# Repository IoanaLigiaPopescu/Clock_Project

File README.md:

BOM

Reference | Qty | Value / Part | JLC Parts Link | Datasheet
U1 | 1 | nRF52840 | https://jlcpcb.com/parts/componentSearch?searchTxt=nRF52840 | https://infocenter.nordicsemi.com/pdf/nRF52840_PS_v1.1.pdf
IC1 | 1 | BQ25180YBGR | https://jlcpcb.com/parts/componentSearch?searchTxt=BQ25180YBGR | https://www.ti.com/lit/ds/symlink/bq25180.pdf
IC2 | 1 | DRV2605YZFR | https://jlcpcb.com/parts/componentSearch?searchTxt=DRV2605YZFR | https://www.ti.com/lit/ds/symlink/drv2605.pdf
IC3 | 1 | BMA421 | https://jlcpcb.com/parts/componentSearch?searchTxt=BMA421 | https://www.bosch-sensortec.com/media/boschsensortec/downloads/datasheets/bst-bma421-ds000.pdf
IC9 | 1 | RT6160AWSC | https://jlcpcb.com/parts/componentSearch?searchTxt=RT6160AWSC | https://www.richtek.com/assets/product_file/RT6160A/DS6160A-00.pdf
U3 | 1 | MAX17048G+T10 | https://jlcpcb.com/parts/componentSearch?searchTxt=MAX17048G+T10 | https://www.analog.com/media/en/technical-documentation/data-sheets/MAX17048-MAX17049.pdf
D3 | 1 | USBLC6-2SC6Y | https://jlcpcb.com/parts/componentSearch?searchTxt=USBLC6-2SC6Y | https://www.st.com/resource/en/datasheet/usblc6-2.pdf
Q1 | 1 | DMG2305UX-7 | https://jlcpcb.com/parts/componentSearch?searchTxt=DMG2305UX-7 | https://www.diodes.com/assets/Datasheets/DMG2305UX.pdf
Q3 | 1 | SI1308EDL-T1-GE3 | https://jlcpcb.com/parts/componentSearch?searchTxt=SI1308EDL | https://www.vishay.com/docs/63399/si1308edl.pdf
J1 | 1 | 503480-2400 | https://jlcpcb.com/parts/componentSearch?searchTxt=503480-2400 | https://www.molex.com/pdm_docs/sd/5034802400_sd.pdf
J2 | 1 | TC2030-IDC | https://jlcpcb.com/parts/componentSearch?searchTxt=TC2030-IDC | https://www.tag-connect.com/wp-content/uploads/bsk-pdf-manager/TC2030-IDC-NL.pdf
J4 | 1 | KH-TYPE-C-16P | https://jlcpcb.com/parts/componentSearch?searchTxt=KH-TYPE-C-16P | https://www.kinghelm.net/uploadfiles/file/20231201/KH-TYPE-C-16P.pdf
ANT1 | 1 | 2450AT18B100E | https://jlcpcb.com/parts/componentSearch?searchTxt=2450AT18B100E | https://www.kyocera-avx.com/docs/techinfo/2450AT18B100.pdf
L7 | 1 | FTC252012SR47MBCA | https://jlcpcb.com/parts/componentSearch?searchTxt=FTC252012SR47MBCA | https://www.fenghua-advanced.com/upload/FTC252012.pdf
SW_DN,SW_ENT,SW_UP | 3 | EVP-AKE31A | https://jlcpcb.com/parts/componentSearch?searchTxt=EVP-AKE31A | https://industrial.panasonic.com/cdbs/www-data/pdf/ABH0000/ABH0000CE116.pdf
X1 | 1 | 32MHz Crystal | https://jlcpcb.com/parts/componentSearch?searchTxt=32MHz crystal 2016 | https://ecsxtal.com/store/pdf/ECS-2016MV.pdf
X2 | 1 | 32.768kHz Crystal | https://jlcpcb.com/parts/componentSearch?searchTxt=32.768kHz crystal 3215 | https://abracon.com/Resonators/ABS07.pdf
C* | multiple | Capacitors 0201/0402 | https://jlcpcb.com/parts/componentSearch?searchTxt=capacitor 0402 | https://www.murata.com/products/productdata/8796745949214/mlcc02e.pdf
R* | multiple | Resistors 0201 | https://jlcpcb.com/parts/componentSearch?searchTxt=resistor 0201 | https://www.yageo.com/upload/media/product/productsearch/datasheet/rchip/PYu-RC_Group_51_RoHS_L_12.pdf
L1,L2,L3,L5 | multiple | Inductors SMD | https://jlcpcb.com/parts/componentSearch?searchTxt=smd inductor | https://www.murata.com/products/productdata/8797098139678/ENFA0008.pdf
TP* | 14 | Test Pads | https://jlcpcb.com/parts/componentSearch?searchTxt=test pad pcb | https://www.keystone-europe.com/downloads/datasheets/5000.pdf

FUNCTIONALITATE

Proiectul este o platformă embedded portabilă bazată pe microcontroller-ul nRF52840, proiectată pentru aplicații low-power cu interfață vizuală E-Paper, alimentare din baterie Li-Po, conectivitate USB-C, feedback haptic și senzori de mișcare. Toate componentele sunt montate pe stratul Top al plăcii PCB.

Microcontroller-ul principal este nRF52840. Acesta integrează procesor ARM Cortex-M4F la 64 MHz, memorie Flash 1 MB, RAM 256 KB și transceiver radio 2.4 GHz compatibil Bluetooth Low Energy. Comunicarea RF se realizează printr-o antenă ceramică 2.45 GHz conectată printr-o rețea de adaptare de impedanță formată din L1, C3, C4 și pad opțional C22 pentru tuning RF. Oscilatorul principal extern este de 32 MHz (X1), iar oscilatorul low-power RTC este de 32.768 kHz (X2).

Interfața USB este realizată prin conector USB Type-C J4. Liniile D+ și D- sunt conectate direct la microcontroller pentru comunicație USB Full Speed. Pinii CC1 și CC2 sunt configurați prin rezistențe de 5.1 kΩ la masă pentru mod Device. Protecția ESD a liniilor USB este realizată de componenta USBLC6-2SC6Y.

Alimentarea principală provine din baterie Li-Po reîncărcabilă. Circuitul de încărcare este BQ25180YBGR, care gestionează încărcarea de la VBUS (5 V USB), controlul curentului de încărcare și monitorizarea stării prin interfață I2C. Tensiunea bateriei este disponibilă pe net-ul BAT și filtrată local prin condensatorul C39.

Conversia de tensiune este realizată de RT6160AWSC, convertor buck-boost controlat prin I2C. Acesta poate ridica sau coborî tensiunea bateriei pentru a genera rail-ul stabilizat necesar sistemului. Etajul de putere utilizează inductanța L7 și condensatorii C23, C24 la intrare respectiv C25, C32 la ieșire.

Monitorizarea nivelului bateriei este realizată de MAX17048G+T10, fuel gauge conectat la magistrala I2C. Acesta măsoară tensiunea celulei și estimează procentul de încărcare, oferind semnal ALERT către microcontroller.

Senzorul de mișcare utilizat este BMA421, accelerometru triaxial low-power. Comunicarea cu microcontroller-ul se face prin I2C, iar liniile INT1 și INT2 permit detectarea de evenimente precum mișcare, tap sau wake-up. Alimentarea senzorului este filtrată prin C18 și C19.

Feedback-ul tactil este realizat prin DRV2605YZFR, driver dedicat pentru motoare ERM/LRA. Acesta este controlat prin I2C și poate genera modele de vibrație prestabilite. Ieșirile OUT+ și OUT- sunt rutate către test point-urile TP_OP și TP_ON.

Interfața vizuală este un display E-Paper conectat prin conector FPC J1 cu 24 pini. Controlul se face de la microcontroller prin semnale dedicate (SPI și GPIO), inclusiv EPD_CS. Circuitul auxiliar al display-ului folosește MOSFET-ul Q3 și componente pasive dedicate pentru generarea tensiunilor necesare panoului.

Interfața utilizator este compusă din trei butoane tactile SW_UP, SW_ENT și SW_DN, conectate la GPIO-urile microcontroller-ului. Acestea permit navigare în meniu și control local fără dispozitive externe.

Programarea și depanarea hardware se realizează prin conectorul J2 compatibil SWD. Sunt disponibile liniile SWDIO, SWDCLK, RESET și SWO. În plus, placa include multiple test point-uri pentru 3.3V, GND, VBAT, SDA, SCL și alte semnale utile în validare.

Magistrala principală de comunicație internă este I2C, partajată între charger, convertorul DC/DC, fuel gauge, IMU și driverul haptic. Aceasta reduce numărul de pini utilizați și simplifică layout-ul PCB.

Estimarea consumului de energie depinde de modul de operare. nRF52840 în sleep poate coborî la ordinul microamperilor. În transmisie radio consumul este de ordinul miliamperilor. Display-ul E-Paper consumă aproape zero în regim static și energie doar la refresh. IMU-ul BMA421 funcționează în mod low-power la câțiva microamperi. Driverul haptic consumă semnificativ doar în timpul vibrației. Autonomia sistemului este favorizată de utilizarea componentelor low-power și a afișajului bistabil.

PCB-ul este proiectat pe 4 straturi, cu planuri dedicate de masă pentru integritate de semnal, zgomot redus și performanță RF mai bună. Toate componentele sunt plasate pe stratul superior pentru asamblare simplificată SMT.

PINI

nRF52840 este microcontroller-ul principal al sistemului și controlează toate perifericele hardware: alimentare, senzori, display, comunicație USB și debugging. Alegerea pinilor a fost făcută pentru a folosi interfețele hardware dedicate și pentru a simplifica rutarea PCB.

Pinii D+ și D- sunt conectați la conectorul USB-C prin protecția ESD D3. Aceștia sunt utilizați pentru comunicație USB nativă, programare și transfer de date.

Pinii SWDIO, SWDCLK, RESET și SWO sunt scoși la conectorul J2 pentru programare și debugging hardware.

P0.07 și P0.08 sunt utilizați ca SDA și SCL pentru magistrala I2C. Pe această magistrală sunt conectate BQ25180 (charger), RT6160A (buck-boost), MAX17048 (fuel gauge), BMA421 (IMU) și DRV2605 (driver haptic). Alegerea I2C reduce numărul de pini utilizați.

P1.08 și P1.09 sunt conectați la INT1 și INT2 de la accelerometru, pentru wake-up la mișcare și notificări hardware.

P0.11 este utilizat pentru semnal de interrupt din zona de power management.

P0.12 este utilizat pentru controlul subsistemului haptic.

P0.06 este utilizat pentru EPD_CS, semnal de selecție al display-ului E-Paper. Restul pinilor display-ului folosesc SPI și GPIO pentru control.

P0.04 și P0.05 sunt pini analogici utilizați pentru măsurători ADC, de exemplu monitorizare tensiune.

Pinul ANT este conectat la rețeaua RF L1, C3, C4 și antena ceramică. Traseul este menținut scurt pentru performanță radio bună.

XC1 și XC2 sunt conectați la cristalul de 32 MHz, iar XL1 și XL2 la cristalul de 32.768 kHz pentru RTC low-power.

PCB-ul este pe 4 straturi, cu plane de masă dedicate și toate componentele pe Top Layer. Antena este plasată la marginea plăcii cu keepout RF. Zona de alimentare este separată de zona RF, iar test point-urile pentru 3.3V, GND, VBAT, SWD și I2C permit depanare rapidă. Designul este optimizat pentru consum redus și funcționare pe baterie.

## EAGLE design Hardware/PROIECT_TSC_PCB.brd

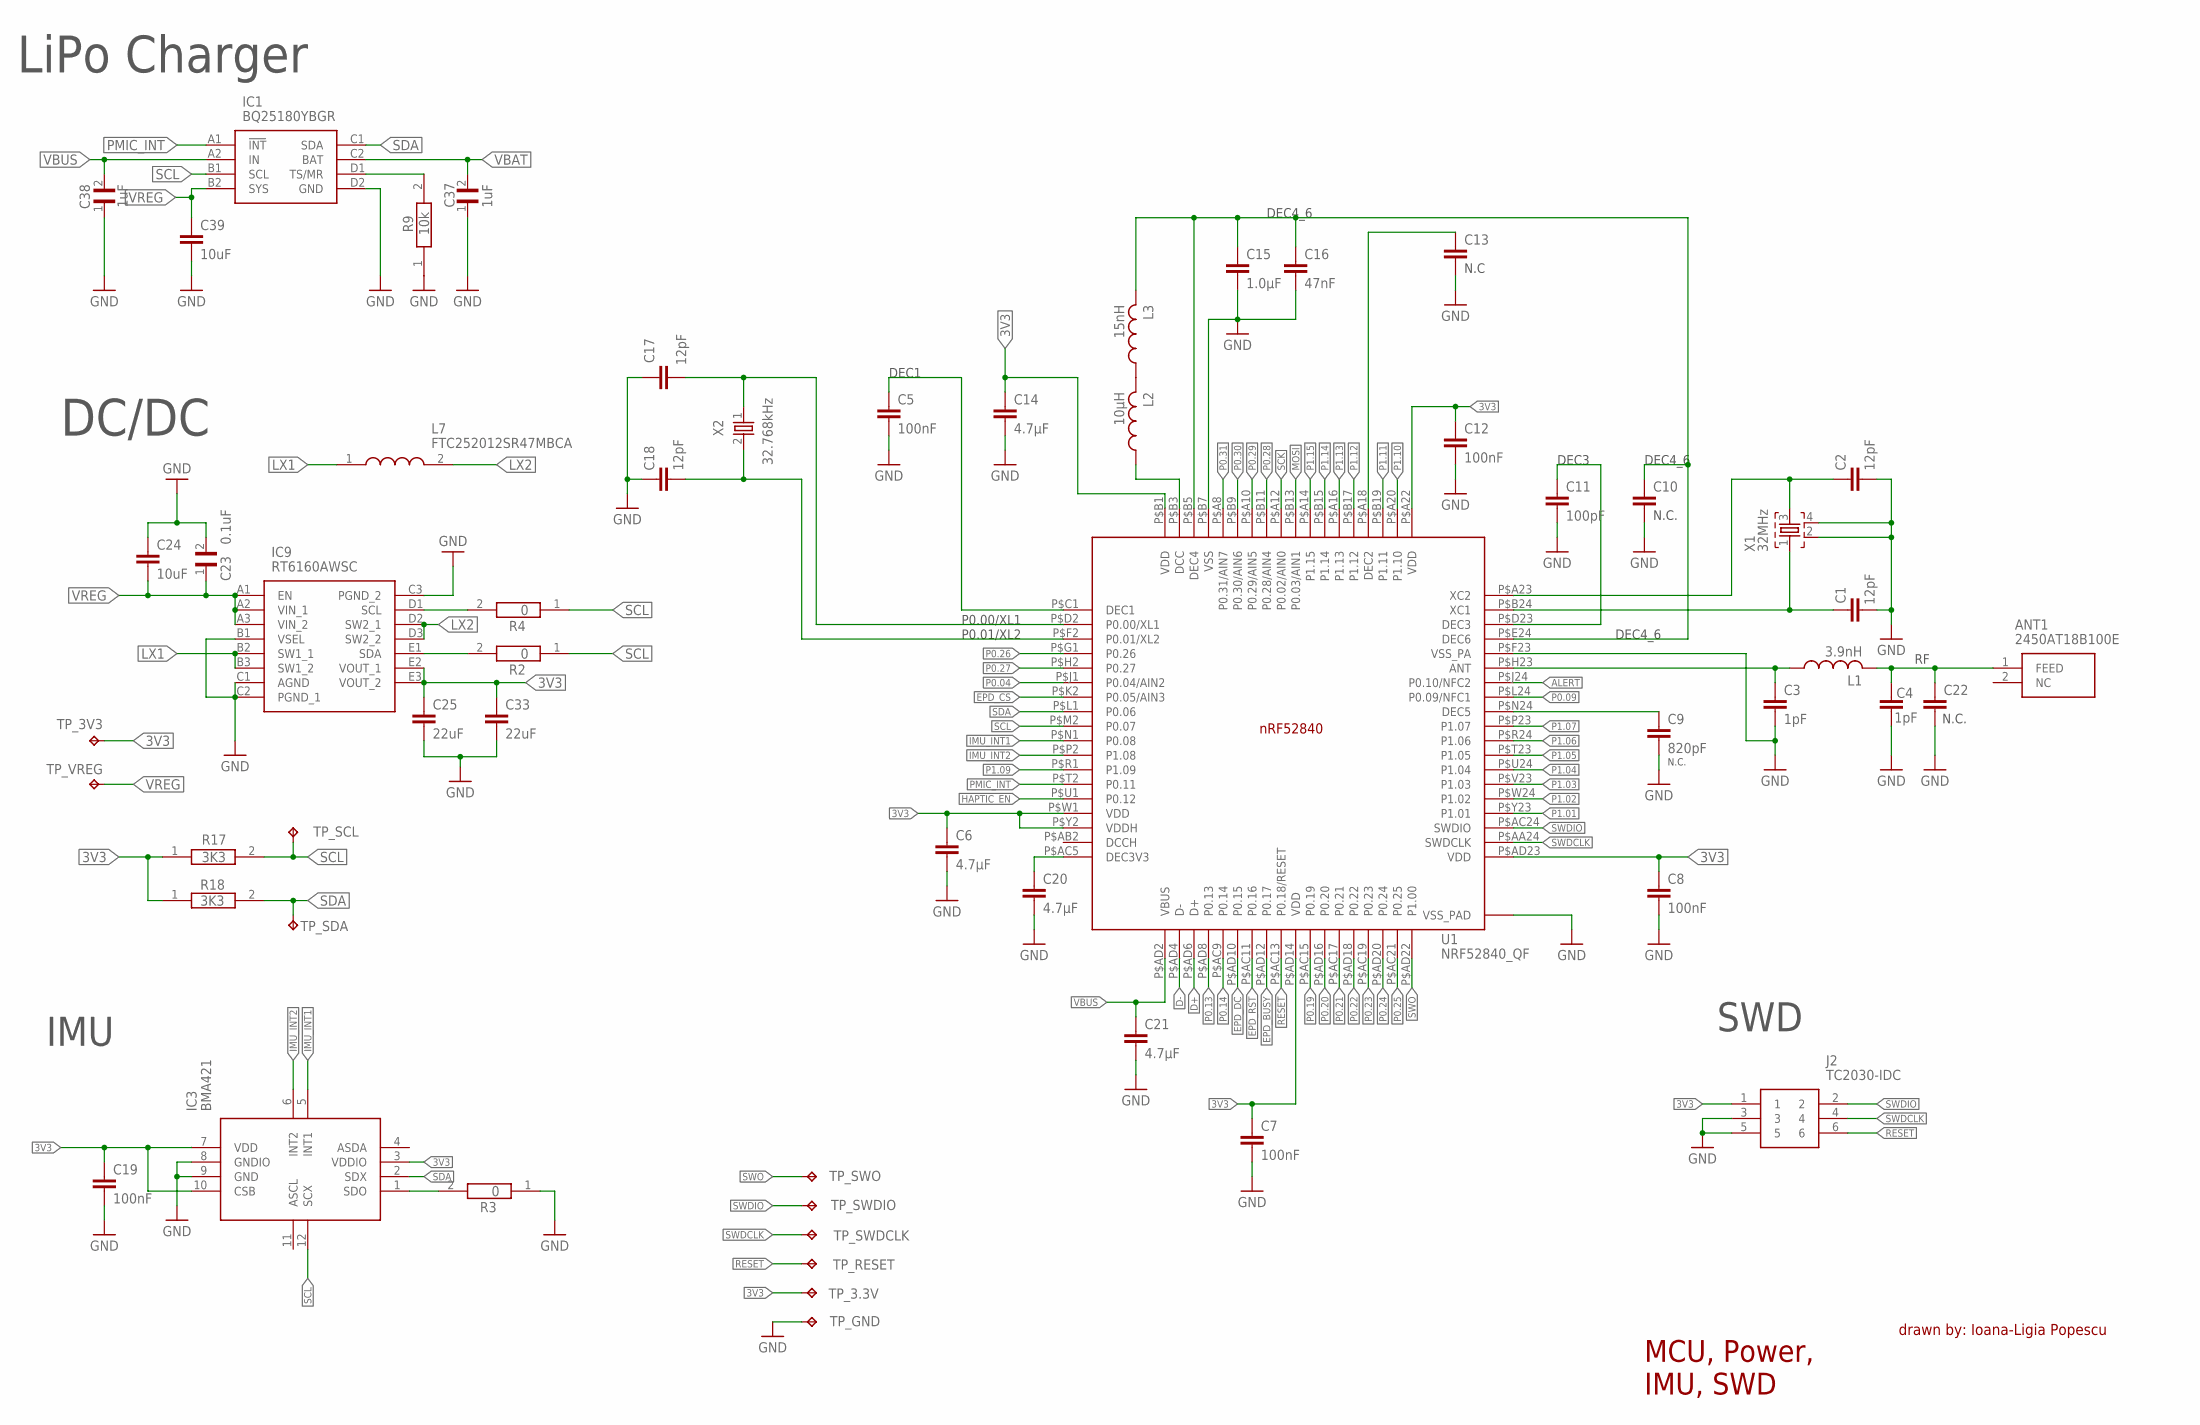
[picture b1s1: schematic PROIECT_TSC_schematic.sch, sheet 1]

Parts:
ANT1: 2450AT18B100E; 2450AT18B100E_ANTC3216X140N
C1, C2, C17, C18: 12pF; NORDIC_NRF_3_RESC0201_L
C3, C4: 1pF; NORDIC_NRF_3_RESC0201_L
C5, C7, C8, C12, C19: 100nF; NORDIC_NRF_3_RESC0201_L
C6, C14, C20, C21: 4.7µF; ESP32_C6_LIBRARY_1_ESP32_WROVER_EAGLE-LTSPICE_C0402
C9: 820pF; NORDIC_NRF_3_RESC0201_L
C10, C13, C22: NORDIC_NRF_3_CAPACITOR_0201_L; NORDIC_NRF_3_RESC0201_L
C11: 100pF; NORDIC_NRF_3_RESC0201_L
C15: 1.0µF; ESP32_C6_LIBRARY_1_ESP32_WROVER_EAGLE-LTSPICE_C0402
C16: 47nF; NORDIC_NRF_3_RESC0201_L
C23: 0.1uF; GRM011R60J152KE01L_2_CAPC0201X13N
C24, C39: 10uF; ESP32_C6_LIBRARY_1_ESP32_WROVER_EAGLE-LTSPICE_C0402
C25, C33: 22uF; ESP32_C6_LIBRARY_1_ESP32_WROVER_EAGLE-LTSPICE_C0402
C37, C38: 1uF; GRM011R60J152KE01L_2_CAPC0201X13N
IC1: BQ25180YBGR; BQ25180YBGR_BGA8C40P2X4_100X155X50
IC3: BMA421; BMA423_BMA423
IC9: RT6160AWSC; RT6160AWSC_BGA15C40P3X5_140X230X60
J2: TC2030-IDC; TC2030-IDC_TC2030IDC
L1: 3.9nH; NORDIC_NRF_2_RESC0402_L
L2: 10µH; NORDIC_NRF_2_RESC0402_L
L3: 15nH; NORDIC_NRF_2_RESC0402_L
L7: FTC252012SR47MBCA; MLP2016SR47MT0S1_INDC2016X100N
R2, R3, R4: 0; CPF0201D7K68C1_0201
R9: 10k; CPF0201D7K68C1_0201
R17, R18: 3K3; CPF0201D7K68C1_0201
TP_3.3V, TP_3V3: HECTOR_WATCH_1_TPTP20R; HECTOR_WATCH_1_TP20R
TP_GND: HECTOR_WATCH_1_TPTP20R; HECTOR_WATCH_1_TP20R
TP_RESET: HECTOR_WATCH_1_TPTP20R; HECTOR_WATCH_1_TP20R
TP_SCL: HECTOR_WATCH_1_TPTP20R; HECTOR_WATCH_1_TP20R
TP_SDA: HECTOR_WATCH_1_TPTP20R; HECTOR_WATCH_1_TP20R
TP_SWDCLK: HECTOR_WATCH_1_TPTP20R; HECTOR_WATCH_1_TP20R
TP_SWDIO: HECTOR_WATCH_1_TPTP20R; HECTOR_WATCH_1_TP20R
TP_SWO: HECTOR_WATCH_1_TPTP20R; HECTOR_WATCH_1_TP20R
TP_VREG: HECTOR_WATCH_1_TPTP20R; HECTOR_WATCH_1_TP20R
U1: NRF52840_QF; NORDIC_NRF_4_AQFN50P700X700X85_HS-74N
X1: 32MHz; NORDIC_NRF_BT-XTAL_2016_N
X2: 32.768kHz; NORDIC_NRF_1_XTAL_3215_N

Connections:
3V3: C6.1, C7.1, C8.1, C12.1, C14.1, C19.1, C25.1, C33.1, IC3.3 (VDDIO), IC3.7 (VDD), IC3.10 (CSB), IC9.E2 (VOUT_1), IC9.E3 (VOUT_2), J2.1, R17.1, R18.1, TP_3.3V.TP, TP_3V3.TP, U1.P$A22 (VDD), U1.P$AD14 (VDD), U1.P$AD23 (VDD), U1.P$B1 (VDD), U1.P$W1 (VDD), U1.P$Y2 (VDDH); also elsewhere on the board
ALERT: U1.P$J24 (P0.10/NFC2); also elsewhere on the board
D+: U1.P$AD6 (D+); also elsewhere on the board
D-: U1.P$AD4 (D-); also elsewhere on the board
EPD_BUSY: U1.P$AD12 (P0.17); also elsewhere on the board
EPD_CS: U1.P$K2 (P0.05/AIN3); also elsewhere on the board
EPD_DC: U1.P$AD10 (P0.15); also elsewhere on the board
EPD_RST: U1.P$AC11 (P0.16); also elsewhere on the board
GND: C1.1, C2.2, C3.2, C4.1, C5.2, C6.2, C7.2, C8.2, C9.2, C10.2, C11.2, C12.2, C13.2, C14.2, C15.2, C16.2, C17.2, C18.1, C19.2, C20.2, C21.2, C22.2, C23.2, C24.1, C25.2, C33.2, C37.1, C38.1, C39.2, IC1.D2 (GND), IC3.8 (GNDIO), IC3.9 (GND), IC9.B1 (VSEL), IC9.C1 (AGND), IC9.C2 (PGND_1), IC9.C3 (PGND_2), J2.3, J2.5, R3.1, R9.1, TP_GND.TP, U1.P$74 (VSS_PAD), U1.P$75 (VSS_PAD), U1.P$76 (VSS_PAD), U1.P$77 (VSS_PAD), U1.P$78 (VSS_PAD), U1.P$79 (VSS_PAD), U1.P$80 (VSS_PAD), U1.P$81 (VSS_PAD), U1.P$82 (VSS_PAD), U1.P$83 (VSS_PAD), U1.P$84 (VSS_PAD), U1.P$85 (VSS_PAD), U1.P$86 (VSS_PAD), U1.P$87 (VSS_PAD), U1.P$88 (VSS_PAD), U1.P$89 (VSS_PAD), U1.P$90 (VSS_PAD), U1.P$B7 (VSS), U1.P$F23 (VSS_PA), X1.2, X1.4; also elsewhere on the board
HAPTIC_EN: U1.P$U1 (P0.12); also elsewhere on the board
IMU_INT1: IC3.5 (INT1), U1.P$N1 (P0.08)
IMU_INT2: IC3.6 (INT2), U1.P$P2 (P1.08)
LX1: IC9.B2 (SW1_1), IC9.B3 (SW1_2), L7.1
LX2: IC9.D2 (SW2_1), IC9.D3 (SW2_2), L7.2
MOSI: U1.P$B13 (P0.03/AIN1); also elsewhere on the board
unnamed: IC1.D1 (TS/MR), R9.2
unnamed: IC9.D1 (SCL), R4.2
unnamed: C11.1, U1.P$D23 (DEC3)
unnamed: IC9.E1 (SDA), R2.2
unnamed: C13.1, U1.P$A18 (DEC2)
unnamed: C2.1, U1.P$A23 (XC2), X1.3
unnamed: C1.2, U1.P$B24 (XC1), X1.1
unnamed: L2.1, U1.P$B3 (DCC)
unnamed: L2.2, L3.1
unnamed: C10.1, C15.1, C16.1, L3.2, U1.P$B5 (DEC4), U1.P$E24 (DEC6)
unnamed: C9.1, U1.P$N24 (DEC5)
unnamed: C3.1, L1.1, U1.P$H23 (ANT)
unnamed: ANT1.1 (FEED), C4.2, C22.1, L1.2
unnamed: C5.1, U1.P$C1 (DEC1)
unnamed: C17.1, U1.P$D2 (P0.00/XL1), X2.1
unnamed: C18.2, U1.P$F2 (P0.01/XL2), X2.2
unnamed: C20.1, U1.P$AC5 (DEC3V3)
unnamed: IC3.1 (SDO), R3.2
P0.04: U1.P$J1 (P0.04/AIN2)
P0.09: U1.P$L24 (P0.09/NFC1)
P0.13: U1.P$AD8 (P0.13); also elsewhere on the board
P0.14: U1.P$AC9 (P0.14); also elsewhere on the board
P0.19: U1.P$AC15 (P0.19)
P0.20: U1.P$AD16 (P0.20)
P0.21: U1.P$AC17 (P0.21)
P0.22: U1.P$AD18 (P0.22)
P0.23: U1.P$AC19 (P0.23)
P0.24: U1.P$AD20 (P0.24)
P0.25: U1.P$AC21 (P0.25)
P0.26: U1.P$G1 (P0.26)
P0.27: U1.P$H2 (P0.27)
P0.28: U1.P$B11 (P0.28/AIN4)
P0.29: U1.P$A10 (P0.29/AIN5)
P0.30: U1.P$B9 (P0.30/AIN6)
P0.31: U1.P$A8 (P0.31/AIN7)
P1.01: U1.P$Y23 (P1.01); also elsewhere on the board
P1.02: U1.P$W24 (P1.02); also elsewhere on the board
P1.03: U1.P$V23 (P1.03)
P1.04: U1.P$U24 (P1.04)
P1.05: U1.P$T23 (P1.05)
P1.06: U1.P$R24 (P1.06)
P1.07: U1.P$P23 (P1.07)
P1.09: U1.P$R1 (P1.09)
P1.10: U1.P$A20 (P1.10)
P1.11: U1.P$B19 (P1.11)
P1.12: U1.P$B17 (P1.12)
P1.13: U1.P$A16 (P1.13)
P1.14: U1.P$B15 (P1.14)
P1.15: U1.P$A14 (P1.15)
PMIC_INT: IC1.A1 (!INT), U1.P$T2 (P0.11)
RESET: J2.6, TP_RESET.TP, U1.P$AC13 (P0.18/RESET)
SCK: U1.P$A12 (P0.02/AIN0); also elsewhere on the board
SCL: IC1.B1 (SCL), IC3.12 (SCX), R2.1, R4.1, R17.2, TP_SCL.TP, U1.P$M2 (P0.07); also elsewhere on the board
SDA: IC1.C1 (SDA), IC3.2 (SDX), R18.2, TP_SDA.TP, U1.P$L1 (P0.06); also elsewhere on the board
SWDCLK: J2.4, TP_SWDCLK.TP, U1.P$AA24 (SWDCLK)
SWDIO: J2.2, TP_SWDIO.TP, U1.P$AC24 (SWDIO)
SWO: TP_SWO.TP, U1.P$AD22 (P1.00)
VBAT: C37.2, IC1.C2 (BAT); also elsewhere on the board
VBUS: C21.1, C38.2, IC1.A2 (IN), U1.P$AD2 (VBUS); also elsewhere on the board
VREG: C23.1, C24.2, C39.1, IC1.B2 (SYS), IC9.A1 (EN), IC9.A2 (VIN_1), IC9.A3 (VIN_2), TP_VREG.TP

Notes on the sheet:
LiPo Charger
DC/DC
N.C.
DEC4_6
DEC3
N.C
DEC1
P0.00/XL1
P0.01/XL2
SWD
IMU
MCU, Power, IMU, SWD
drawn by: Ioana-Ligia Popescu

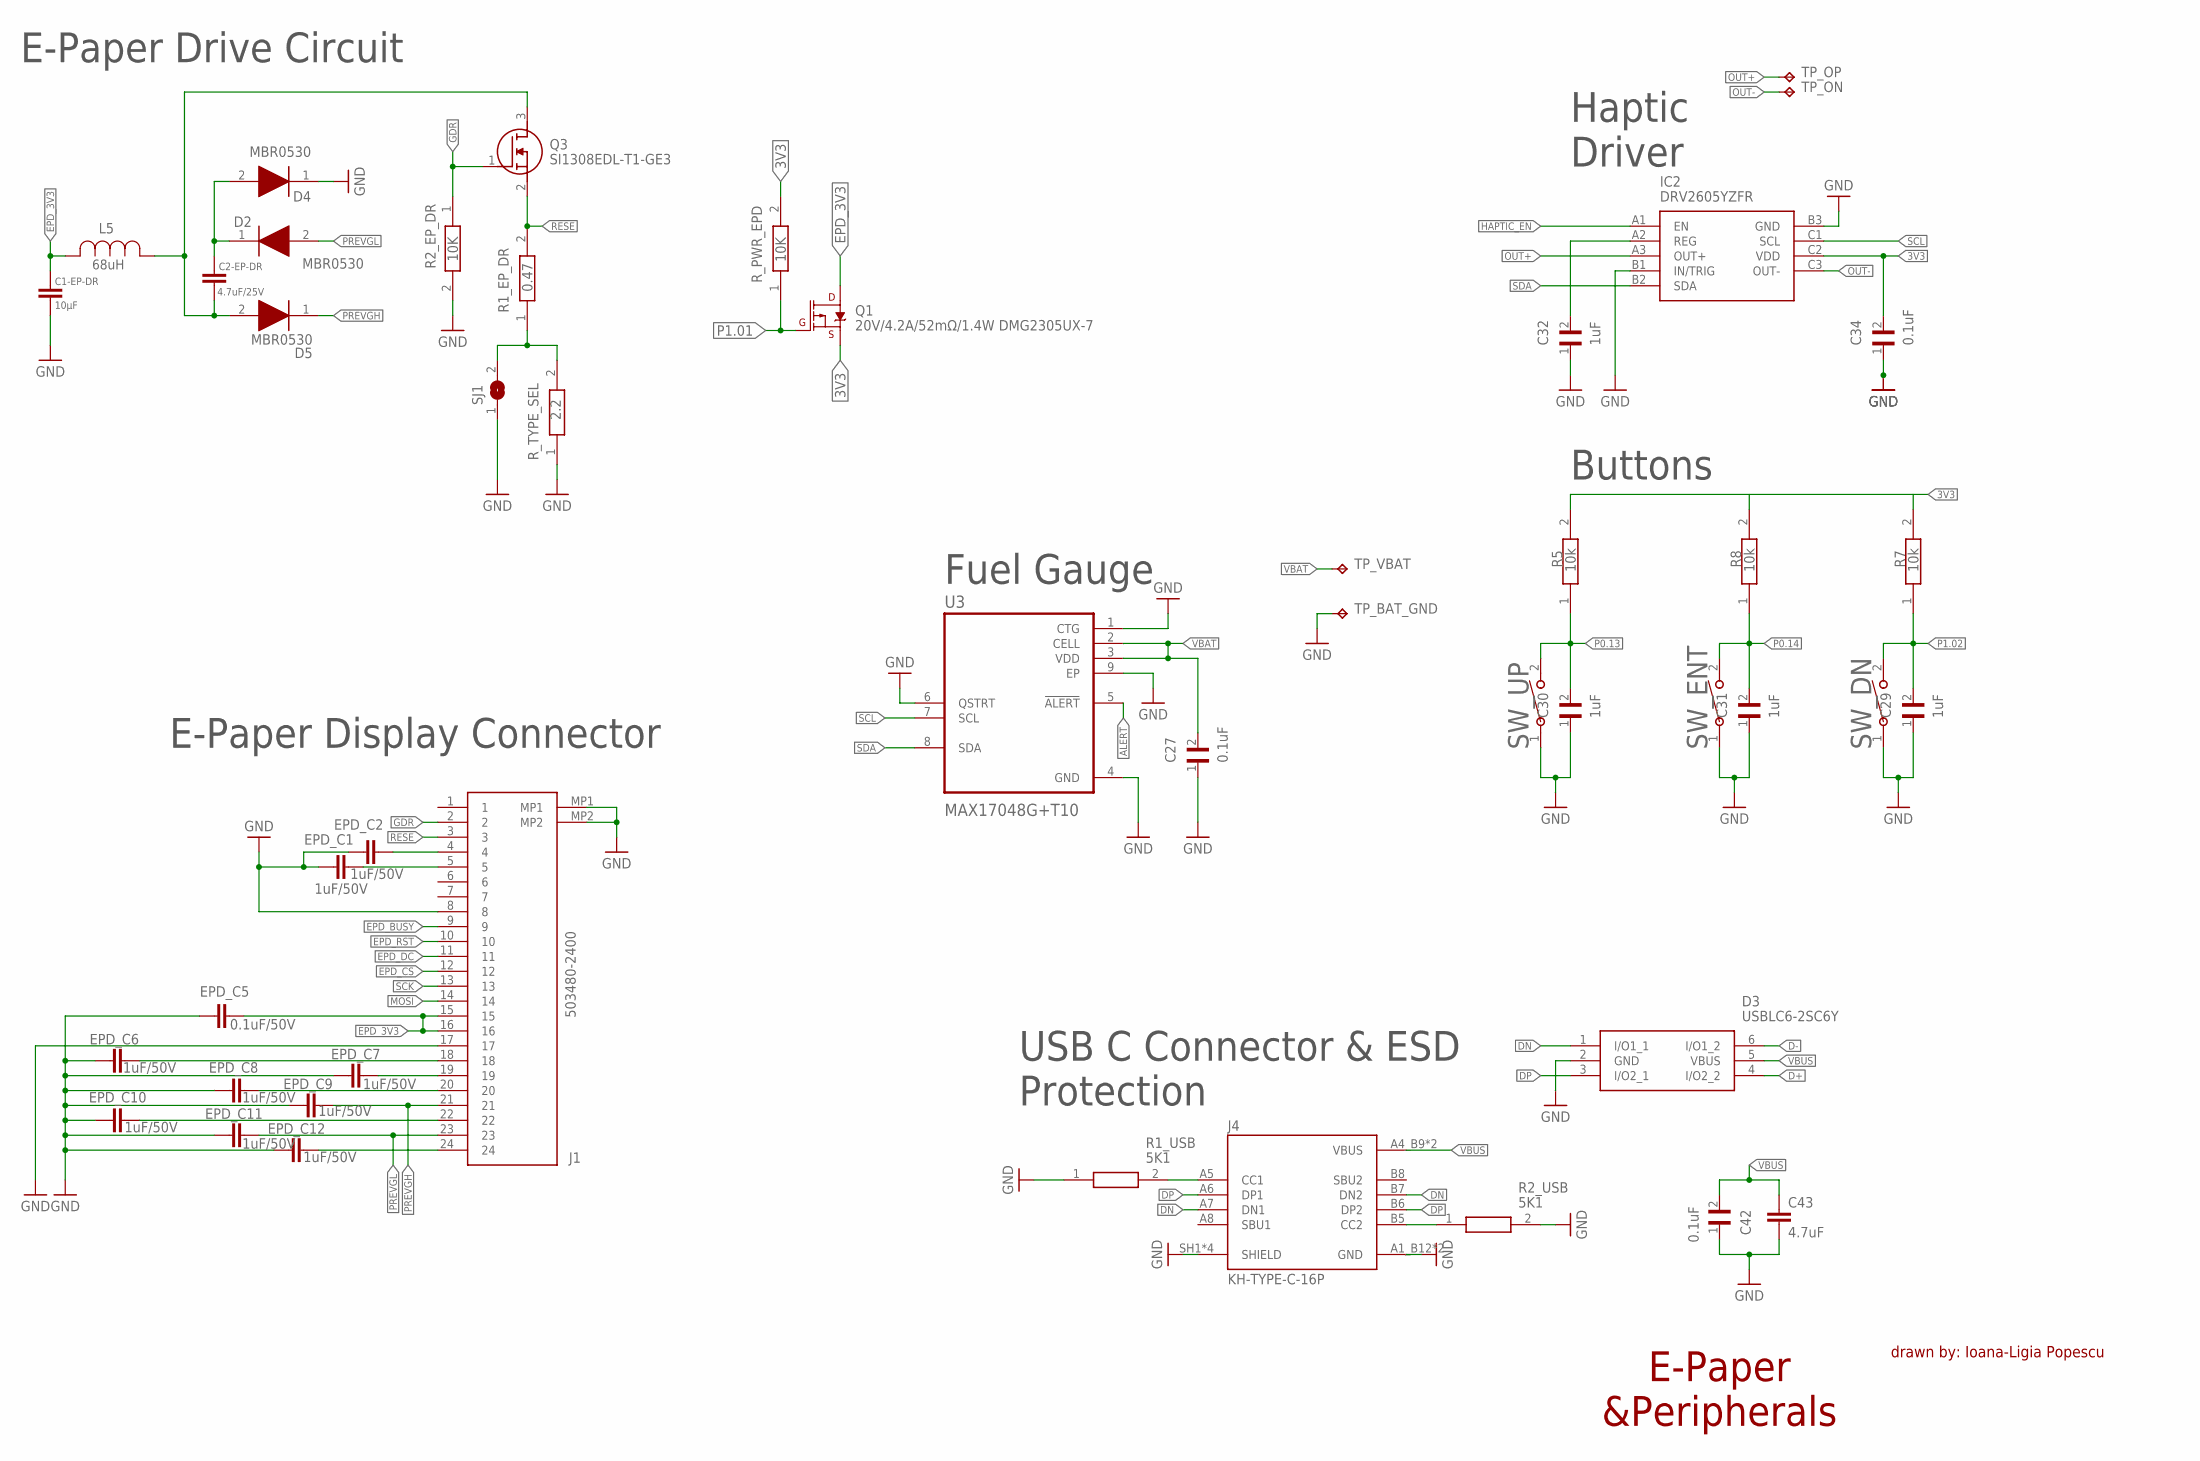
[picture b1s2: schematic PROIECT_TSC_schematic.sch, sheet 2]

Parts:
C1-EP-DR: 10µF; ESP32_C6_LIBRARY_1_ESP32_WROVER_EAGLE-LTSPICE_C0402
C2-EP-DR: 4.7uF/25V; ESP32_C6_LIBRARY_1_ESP32_WROVER_EAGLE-LTSPICE_C0402
C27, C34, C42: 0.1uF; GRM011R60J152KE01L_2_CAPC0201X13N
C29, C30, C31, C32: 1uF; GRM011R60J152KE01L_2_CAPC0201X13N
C43: 4.7uF; ESP32_C6_LIBRARY_1_ESP32_WROVER_EAGLE-LTSPICE_C0402
D2, D4, D5: MBR0530; ESP32_C6_LIBRARY_5_SOD3716X135N
D3: USBLC6-2SC6Y; ESP32_C6_LIBRARY_3_SOT95P280X145-6N
EPD_C1, EPD_C2, EPD_C6, EPD_C7, EPD_C8, EPD_C9, EPD_C10, EPD_C11, EPD_C12: 1uF/50V; ESP32_C6_LIBRARY_1_ESP32_WROVER_EAGLE-LTSPICE_C0402
EPD_C5: 0.1uF/50V; ESP32_C6_LIBRARY_1_ESP32_WROVER_EAGLE-LTSPICE_C0402
IC2: DRV2605YZFR; DRV2605YZFR_BGA9C50P3X3_144X144X62
J1: 503480-2400; 503480-2400_5034802400
J4: KH-TYPE-C-16P; KH-TYPE-C-16P_KINGHELM_KH-TYPE-C-16P
L5: 68uH; ESP32_C6_LIBRARY_2_IND_4828-WE-TPC_WRE
Q1: 20V/4.2A/52mΩ/1.4W DMG2305UX-7; ESP32_C6_LIBRARY_4_ESP32_C6_LIBRARY_4_ESP32_C6_LIBRARY_4_ES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
Q3: SI1308EDL-T1-GE3; ESP32_C6_LIBRARY_6_SOT65P210X110-3N
R1_EP_DR: 0.47; CPF0201D7K68C1_0201
R1_USB, R2_USB: 5K1; CPF0201D7K68C1_0201
R2_EP_DR: 10K; CPF0201D7K68C1_0201
R5, R7, R8: 10k; CPF0201D7K68C1_0201
R_PWR_EPD: 10K; CPF0201D7K68C1_0201
R_TYPE_SEL: 2.2; CPF0201D7K68C1_0201
SJ1: ESP32_C6_LIBRARY_7_JUMPER_SJ
SW_DN: 2025-10-22_07-23-44_LIBRARY_EVP-AKE31ASW_EVP-AKE3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; 2025-10-22_07-23-44_LIBRARY_SW_EVP-AKE31A_PAN
SW_ENT: 2025-10-22_07-23-44_LIBRARY_EVP-AKE31ASW_EVP-AKE3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; 2025-10-22_07-23-44_LIBRARY_SW_EVP-AKE31A_PAN
SW_UP: 2025-10-22_07-23-44_LIBRARY_EVP-AKE31ASW_EVP-AKE3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; 2025-10-22_07-23-44_LIBRARY_SW_EVP-AKE31A_PAN
TP_BAT_GND: HECTOR_WATCH_1_TPTP20R; HECTOR_WATCH_1_TP20R
TP_ON: HECTOR_WATCH_1_TPTP20R; HECTOR_WATCH_1_TP20R
TP_OP: HECTOR_WATCH_1_TPTP20R; HECTOR_WATCH_1_TP20R
TP_VBAT: HECTOR_WATCH_1_TPTP20R; HECTOR_WATCH_1_TP20R
U3: MAX17048G+T10; ESP32_C6_LIBRARY_SON50P200X200X80-9N

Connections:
3V3: C34.2, IC2.C2 (VDD), Q1.2 (S), R5.2, R_PWR_EPD.2; also elsewhere on the board
ALERT: U3.5 (!ALERT); also elsewhere on the board
D+: D3.4 (I/O2_2); also elsewhere on the board
D-: D3.6 (I/O1_2); also elsewhere on the board
DN: D3.1 (I/O1_1), J4.A7 (DN1), J4.B7 (DN2)
DP: D3.3 (I/O2_1), J4.A6 (DP1), J4.B6 (DP2)
EPD_3V3: C1-EP-DR.1, EPD_C5.2, J1.15, J1.16, L5.2, Q1.3 (D)
EPD_BUSY: J1.9; also elsewhere on the board
EPD_CS: J1.12; also elsewhere on the board
EPD_DC: J1.11; also elsewhere on the board
EPD_RST: J1.10; also elsewhere on the board
GDR: J1.2, Q3.1 (G), R2_EP_DR.1
GND: C1-EP-DR.2, C27.1, C29.1, C30.1, C31.1, C32.1, C34.1, C42.1, C43.2, D3.2 (GND), D4.1 (K), EPD_C1.1, EPD_C2.1, EPD_C5.1, EPD_C6.1, EPD_C7.1, EPD_C8.1, EPD_C9.1, EPD_C10.1, EPD_C11.1, EPD_C12.1, IC2.B1 (IN/TRIG), IC2.B3 (GND), J1.8, J1.17, J1.MP1, J1.MP2, J4.A1_B12 (GND), J4.A12_B1 (GND), J4.SH1 (SHIELD), J4.SH2 (SHIELD), J4.SH3 (SHIELD), J4.SH4 (SHIELD), R1_USB.1, R2_EP_DR.2, R2_USB.2, R_TYPE_SEL.1, SJ1.1, SW_DN.1, SW_ENT.1, SW_UP.1, TP_BAT_GND.TP, U3.1 (CTG), U3.4 (GND), U3.6 (QSTRT), U3.9 (EP); also elsewhere on the board
HAPTIC_EN: IC2.A1 (EN); also elsewhere on the board
MOSI: J1.14; also elsewhere on the board
unnamed: C2-EP-DR.2, D5.2 (A), L5.1, Q3.3 (D)
unnamed: C2-EP-DR.1, D2.1 (K), D4.2 (A)
unnamed: R1_EP_DR.1, R_TYPE_SEL.2, SJ1.2
unnamed: EPD_C2.2, J1.4
unnamed: EPD_C1.2, J1.5
unnamed: J4.B5 (CC2), R2_USB.1
unnamed: C32.2, IC2.A2 (REG)
unnamed: J4.A5 (CC1), R1_USB.2
unnamed: EPD_C6.2, J1.18
unnamed: EPD_C7.2, J1.19
unnamed: EPD_C8.2, J1.20
unnamed: EPD_C10.2, J1.22
unnamed: EPD_C12.2, J1.24
OUT+: IC2.A3 (OUT+), TP_OP.TP
OUT-: IC2.C3 (OUT-), TP_ON.TP
P0.13: C30.2, R5.1, SW_UP.2; also elsewhere on the board
P0.14: C31.2, R8.1, SW_ENT.2; also elsewhere on the board
P1.01: Q1.1 (G), R_PWR_EPD.1; also elsewhere on the board
P1.02: C29.2, R7.1, SW_DN.2; also elsewhere on the board
PREVGH: D5.1 (K), EPD_C9.2, J1.21
PREVGL: D2.2 (A), EPD_C11.2, J1.23
RESE: J1.3, Q3.2 (S), R1_EP_DR.2
SCK: J1.13; also elsewhere on the board
SCL: IC2.C1 (SCL), U3.7 (SCL); also elsewhere on the board
SDA: IC2.B2 (SDA), U3.8 (SDA); also elsewhere on the board
VBAT: C27.2, TP_VBAT.TP, U3.2 (CELL), U3.3 (VDD); also elsewhere on the board
VBUS: C42.2, C43.1, D3.5 (VBUS), J4.A4_B9 (VBUS), J4.A9_B4 (VBUS); also elsewhere on the board

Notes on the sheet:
E-Paper Drive Circuit
Haptic Driver
E-Paper Display Connector
USB C Connector & ESD Protection
Buttons
Fuel Gauge
E-Paper &Peripherals
drawn by: Ioana-Ligia Popescu

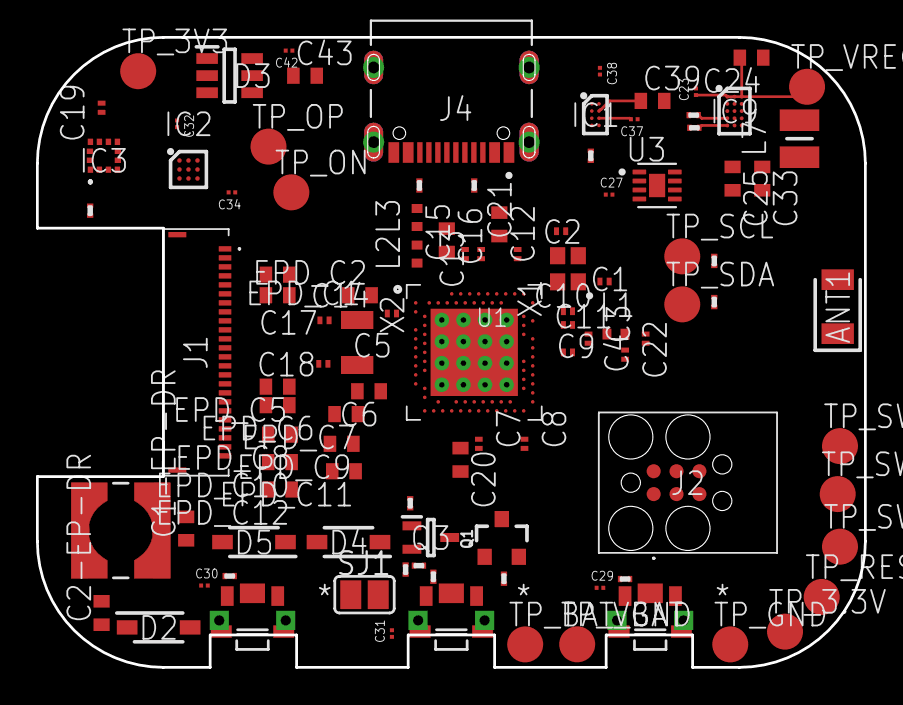
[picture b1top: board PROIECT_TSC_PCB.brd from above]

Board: 4 copper layers, 46.0 x 35.0 mm, 105 parts (0 on the bottom side), 70 nets.

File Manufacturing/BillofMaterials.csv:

Reference Designators;Quantity;Description;Package;Value;Manufacturer;Manufacturer Part Number;Vendor;Vendor Part Number;Top/Bottom;
;1;PCB Board;Board;;;;;;;
ANT1;1;Antennas 2.45GHz ANTENNA;2450AT18B100E_ANTC3216X140N;2450AT18B100E;;;;;Top;
C1, C2, C17, C18;4;Generic chip capacitor;NORDIC_NRF_3_RESC0201_L;12pF;;;;;Top;
C1-EP-DR;1;CAPACITOR, European symbol;ESP32_WROVER_EAGLE-LTSPICE_C0402;10µF;;;;;Top;
C2-EP-DR;1;CAPACITOR, European symbol;ESP32_WROVER_EAGLE-LTSPICE_C0402;4.7uF/25V;;;;;Top;
C3, C4;2;Generic chip capacitor;NORDIC_NRF_3_RESC0201_L;1pF;;;;;Top;
C5, C7, C8, C12, C19;5;Generic chip capacitor;NORDIC_NRF_3_RESC0201_L;100nF;;;;;Top;
C6, C14, C20, C21;4;CAPACITOR, European symbol;ESP32_WROVER_EAGLE-LTSPICE_C0402;4.7µF;;;;;Top;
C9;1;Generic chip capacitor;NORDIC_NRF_3_RESC0201_L;820pF;;;;;Top;
C10, C13, C22;3;Generic chip capacitor;NORDIC_NRF_3_RESC0201_L;;;;;;Top;
C11;1;Generic chip capacitor;NORDIC_NRF_3_RESC0201_L;100pF;;;;;Top;
C15;1;CAPACITOR, European symbol;ESP32_WROVER_EAGLE-LTSPICE_C0402;1.0µF;;;;;Top;
C16;1;Generic chip capacitor;NORDIC_NRF_3_RESC0201_L;47nF;;;;;Top;
C23, C27, C34, C42;4;Check availability;CAPC0201X13N;0.1uF;;;;;Top;
C24, C39;2;CAPACITOR, European symbol;ESP32_WROVER_EAGLE-LTSPICE_C0402;10uF;;;;;Top;
C25, C33;2;CAPACITOR, European symbol;ESP32_WROVER_EAGLE-LTSPICE_C0402;22uF;;;;;Top;
C29, C30, C31, C32, C37, C38;6;Check availability;CAPC0201X13N;1uF;;;;;Top;
C43;1;CAPACITOR, European symbol;ESP32_WROVER_EAGLE-LTSPICE_C0402;4.7uF;;;;;Top;
D2, D4, D5;3;ON SEMICONDUCTOR - MBR0530 - DIODE, SCHOTTKY, 0.5A, 30V, SOD-123;SOD3716X135N;MBR0530;;;;;Top;
D3;1;Low Cap. ESD Protection Auto SOT-23-6 STMicroelectronics USBLC6-2SC6Y, Dual Uni-Directional TVS Diode Array, 6-Pin SOT-23;SOT95P280X145-6N;USBLC6-2SC6Y;;;;;Top;
EPD_C1, EPD_C2, EPD_C6, EPD_C7, EPD_C8, EPD_C9, EPD_C10, EPD_C11, EPD_C12;9;CAPACITOR, European symbol;ESP32_WROVER_EAGLE-LTSPICE_C0402;1uF/50V;;;;;Top;
EPD_C5;1;CAPACITOR, European symbol;ESP32_WROVER_EAGLE-LTSPICE_C0402;0.1uF/50V;;;;;Top;
IC1;1;Charger IC Lithium Ion/Polymer, Lithium Iron Phosphate 8-DSBGA (1.6x1.1);BQ25180YBGR_BGA8C40P2X4_100X155X50;BQ25180YBGR;;;;;Top;
IC2;1;Haptic Driver for ERM/LRA with Built-In Library and Smart Loop Architecture;DRV2605YZFR_BGA9C50P3X3_144X144X62;DRV2605YZFR;;;;;Top;
IC3;1;Accelerometers Triaxial low-g 12bit Acceleration Sensor;BMA423_BMA423;BMA421;;;;;Top;
IC9;1;Buck-Boost Regulator Positive Output Step-Up/Step-Down I2C DC-DC Controller IC 15-WL-CSP (BSC) (1.4x2.3);RT6160AWSC_BGA15C40P3X5_140X230X60;RT6160AWSC;;;;;Top;
J1;1;FFC & FPC Connectors 0.5mm FPC RA SMT Dual Contact 24Ckt;503480-2400_5034802400;503480-2400;;;;;Top;
J2;1;CABLE ADAPTER 6 POS;TC2030-IDC_TC2030IDC;TC2030-IDC;;;;;Top;
J4;1;Check availability;KINGHELM_KH-TYPE-C-16P;KH-TYPE-C-16P;;;;;Top;
L1;1;Generic chip inductor;NORDIC_NRF_2_RESC0402_L;3.9nH;;;;;Top;
L2;1;Generic chip inductor;NORDIC_NRF_2_RESC0402_L;10µH;;;;;Top;
L3;1;Generic chip inductor;NORDIC_NRF_2_RESC0402_L;15nH;;;;;Top;
L5;1;;ESP32_C6_LIBRARY_2_IND_4828-WE-TPC_WRE;68uH;;;;;Top;
L7;1;SMD / SMT Inductors (Coils), L=0.47?H, L x W x T :;MLP2016SR47MT0S1_INDC2016X100N;FTC252012SR47MBCA;;;;;Top;
Q1;1;P-channel MOSFETs;ESP32_WROVER_SPARKFUN-DISCRETESEMI_SOT23-3;20V/4.2A/52mΩ/1.4W DMG2305UX-7;;;;;Top;
Q3;1;MOSFET N-Ch 30V 1.5A TrenchFET SC70 Vishay Si1308EDL-T1-GE3 N-channel MOSFET Transistor, 1.5 A, 30 V, 3-Pin SC-70;SOT65P210X110-3N;SI1308EDL-T1-GE3;;;;;Top;
R_PWR_EPD, R2_EP_DR;2;7.68k 0201 Thin Film Surface Mount Fixed Resistor +/-0.5% 0.031W CPF0201D7K68C1;CPF0201D7K68C1_0201;10K;;;;;Top;
R_TYPE_SEL;1;7.68k 0201 Thin Film Surface Mount Fixed Resistor +/-0.5% 0.031W CPF0201D7K68C1;CPF0201D7K68C1_0201;2.2;;;;;Top;
R1_EP_DR;1;7.68k 0201 Thin Film Surface Mount Fixed Resistor +/-0.5% 0.031W CPF0201D7K68C1;CPF0201D7K68C1_0201;0.47;;;;;Top;
R1_USB, R2_USB;2;7.68k 0201 Thin Film Surface Mount Fixed Resistor +/-0.5% 0.031W CPF0201D7K68C1;CPF0201D7K68C1_0201;5K1;;;;;Top;
R2, R3, R4;3;7.68k 0201 Thin Film Surface Mount Fixed Resistor +/-0.5% 0.031W CPF0201D7K68C1;CPF0201D7K68C1_0201;0;;;;;Top;
R5, R7, R8, R9;4;7.68k 0201 Thin Film Surface Mount Fixed Resistor +/-0.5% 0.031W CPF0201D7K68C1;CPF0201D7K68C1_0201;10k;;;;;Top;
R17, R18;2;7.68k 0201 Thin Film Surface Mount Fixed Resistor +/-0.5% 0.031W CPF0201D7K68C1;CPF0201D7K68C1_0201;3K3;;;;;Top;
SJ1;1;SMD solder JUMPER;JUMPER_SJ;;;;;;Top;
SW_DN, SW_ENT, SW_UP;3;;SW_EVP-AKE31A_PAN;2025-10-22_07-23-44_LIBRARY_EVP-AKE31ASW_EVP-AKE31A_PAN;;;;;Top;
TP_3.3V, TP_3V3, TP_BAT_GND, TP_GND, TP_ON, TP_OP, TP_RESET, TP_SCL, TP_SDA, TP_SWDCLK, TP_SWDIO, TP_SWO, TP_VBAT, TP_VREG;14;Test pad;HECTOR_WATCH_1_TP20R;HECTOR_WATCH_1_TPTP20R;;;;;Top;
U1;1;nRF52840;NORDIC_NRF_4_AQFN50P700X700X85_HS-74N;NRF52840_QF;;;;;Top;
U3;1;Check availability;SON50P200X200X80-9N;MAX17048G+T10;;;;;Top;
X1;1;;NORDIC_NRF_BT-XTAL_2016_N;32MHz;;;;;Top;
X2;1;;NORDIC_NRF_1_XTAL_3215_N;32.768kHz;;;;;Top;

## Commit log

2026-04-20 reorganize final
2026-04-20 image

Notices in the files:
parts and their libraries:
COPYRIGHT: Copyright (C) 2024 Ultra Librarian. All rights reserved.
COPYRIGHT: Copyright (C) 2025 Ultra Librarian. All rights reserved.
